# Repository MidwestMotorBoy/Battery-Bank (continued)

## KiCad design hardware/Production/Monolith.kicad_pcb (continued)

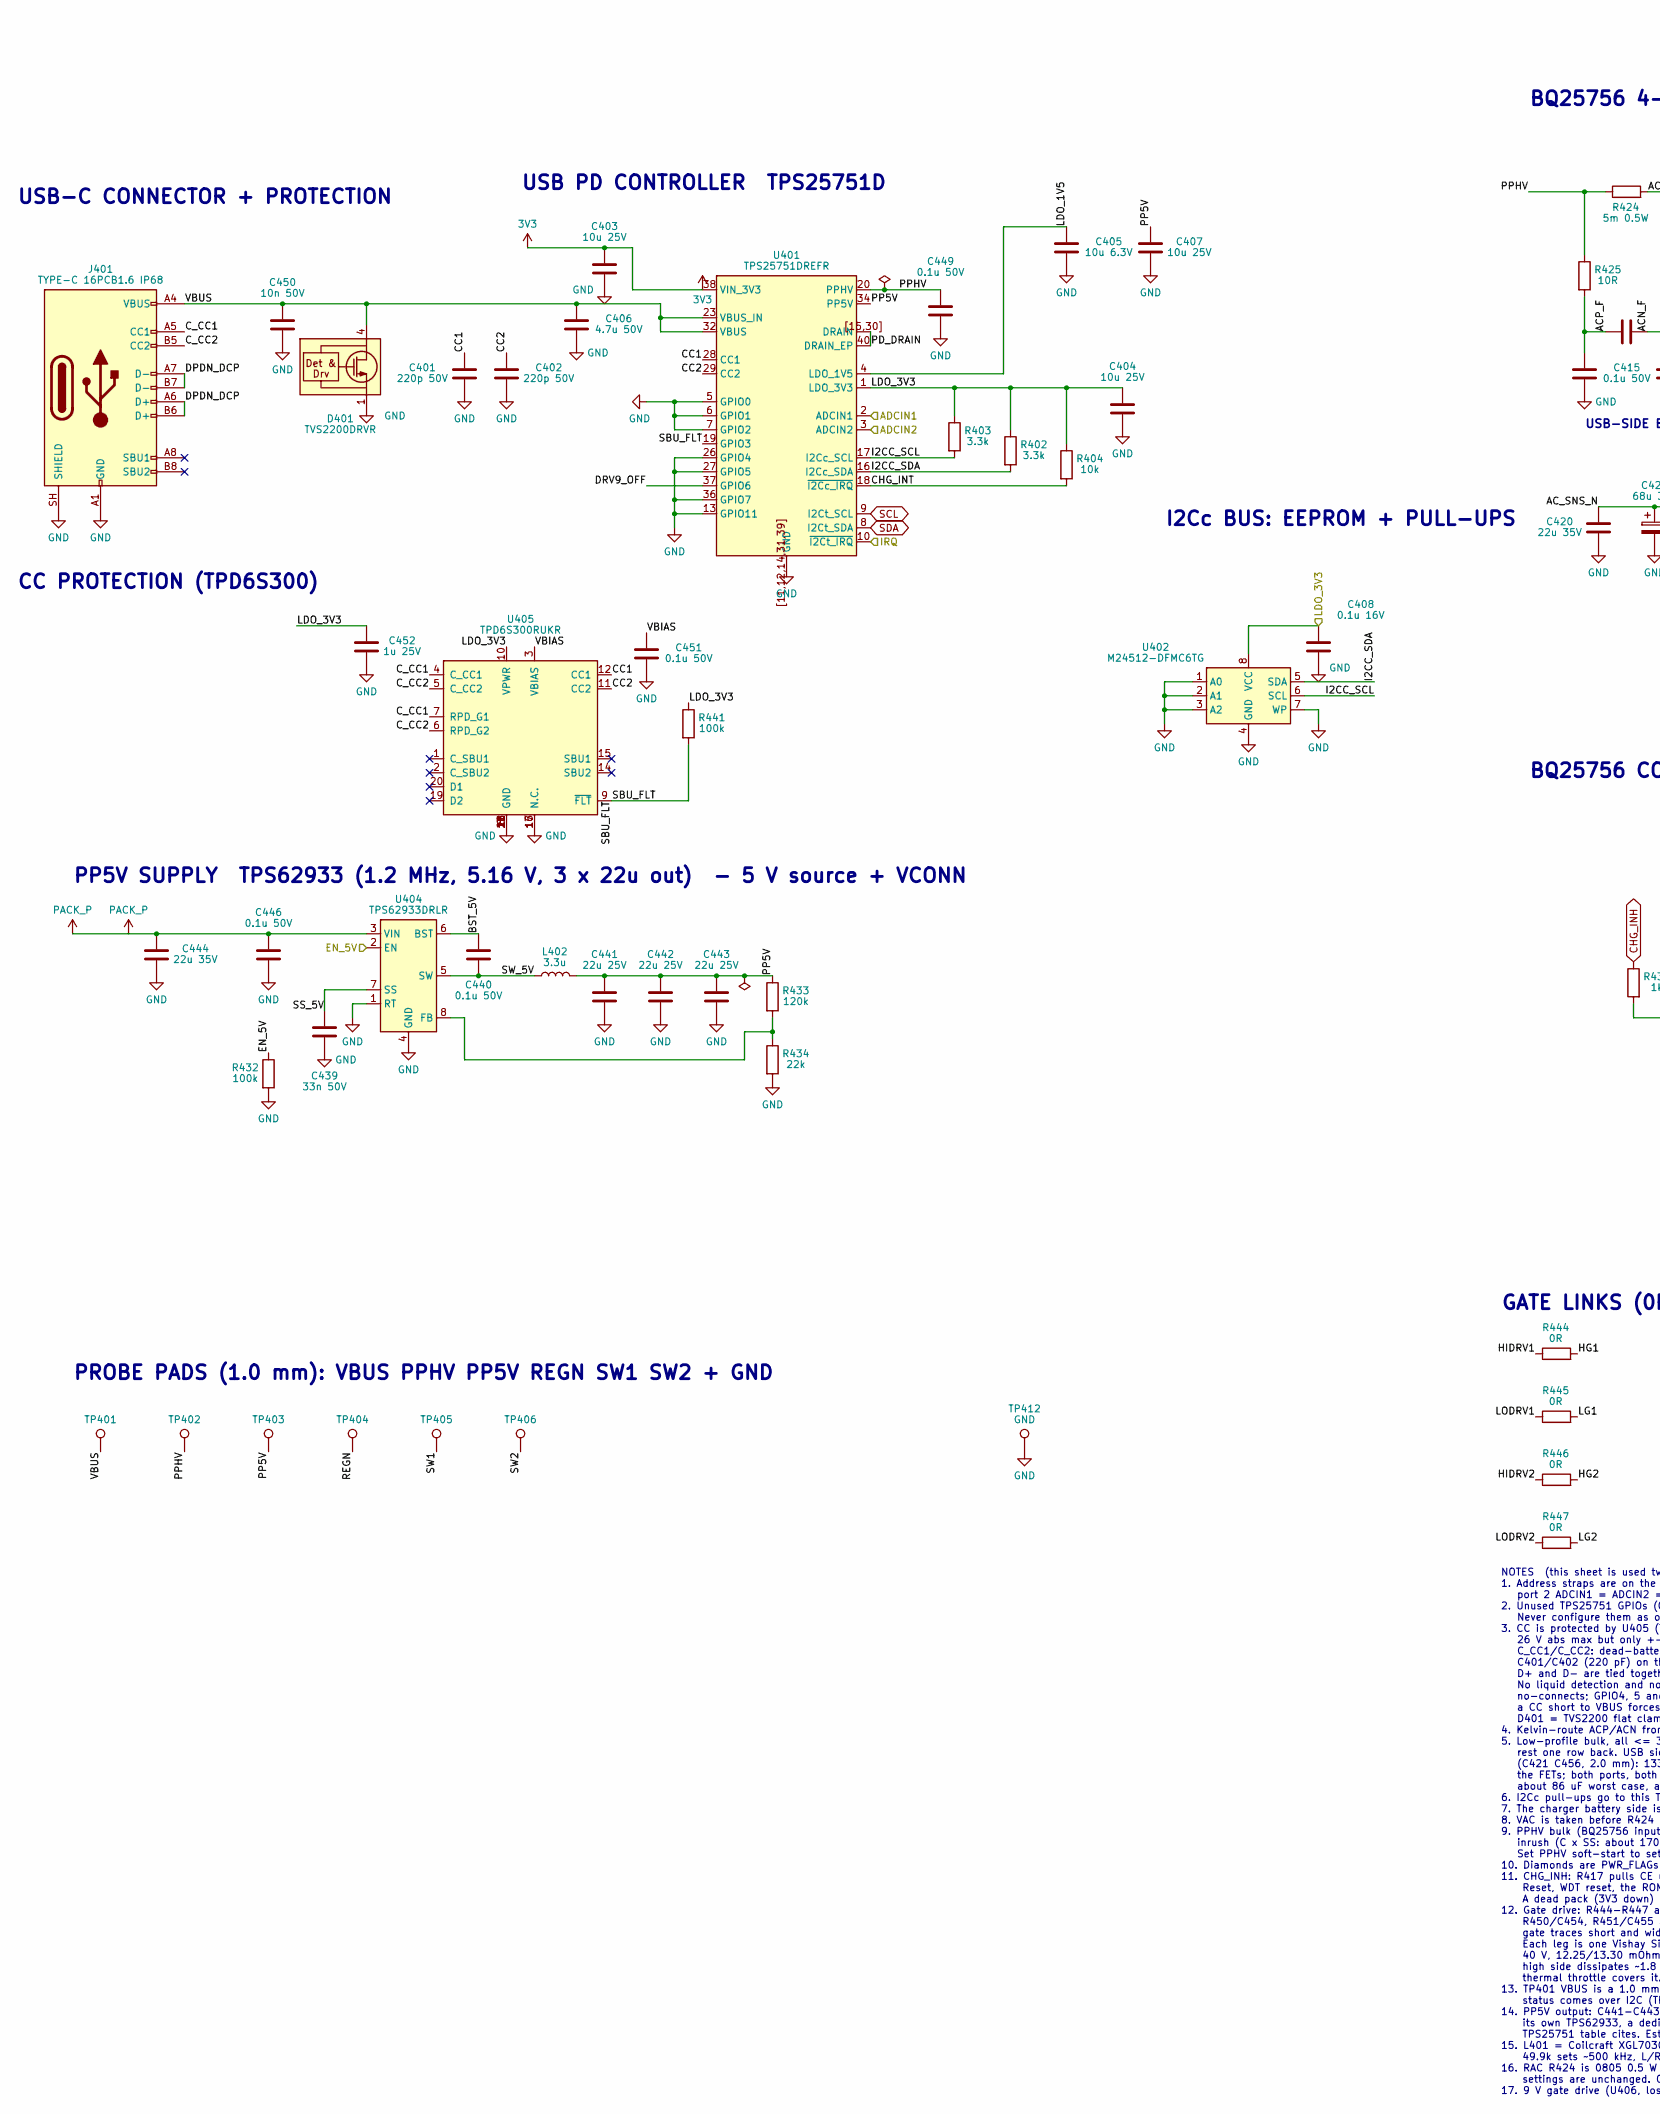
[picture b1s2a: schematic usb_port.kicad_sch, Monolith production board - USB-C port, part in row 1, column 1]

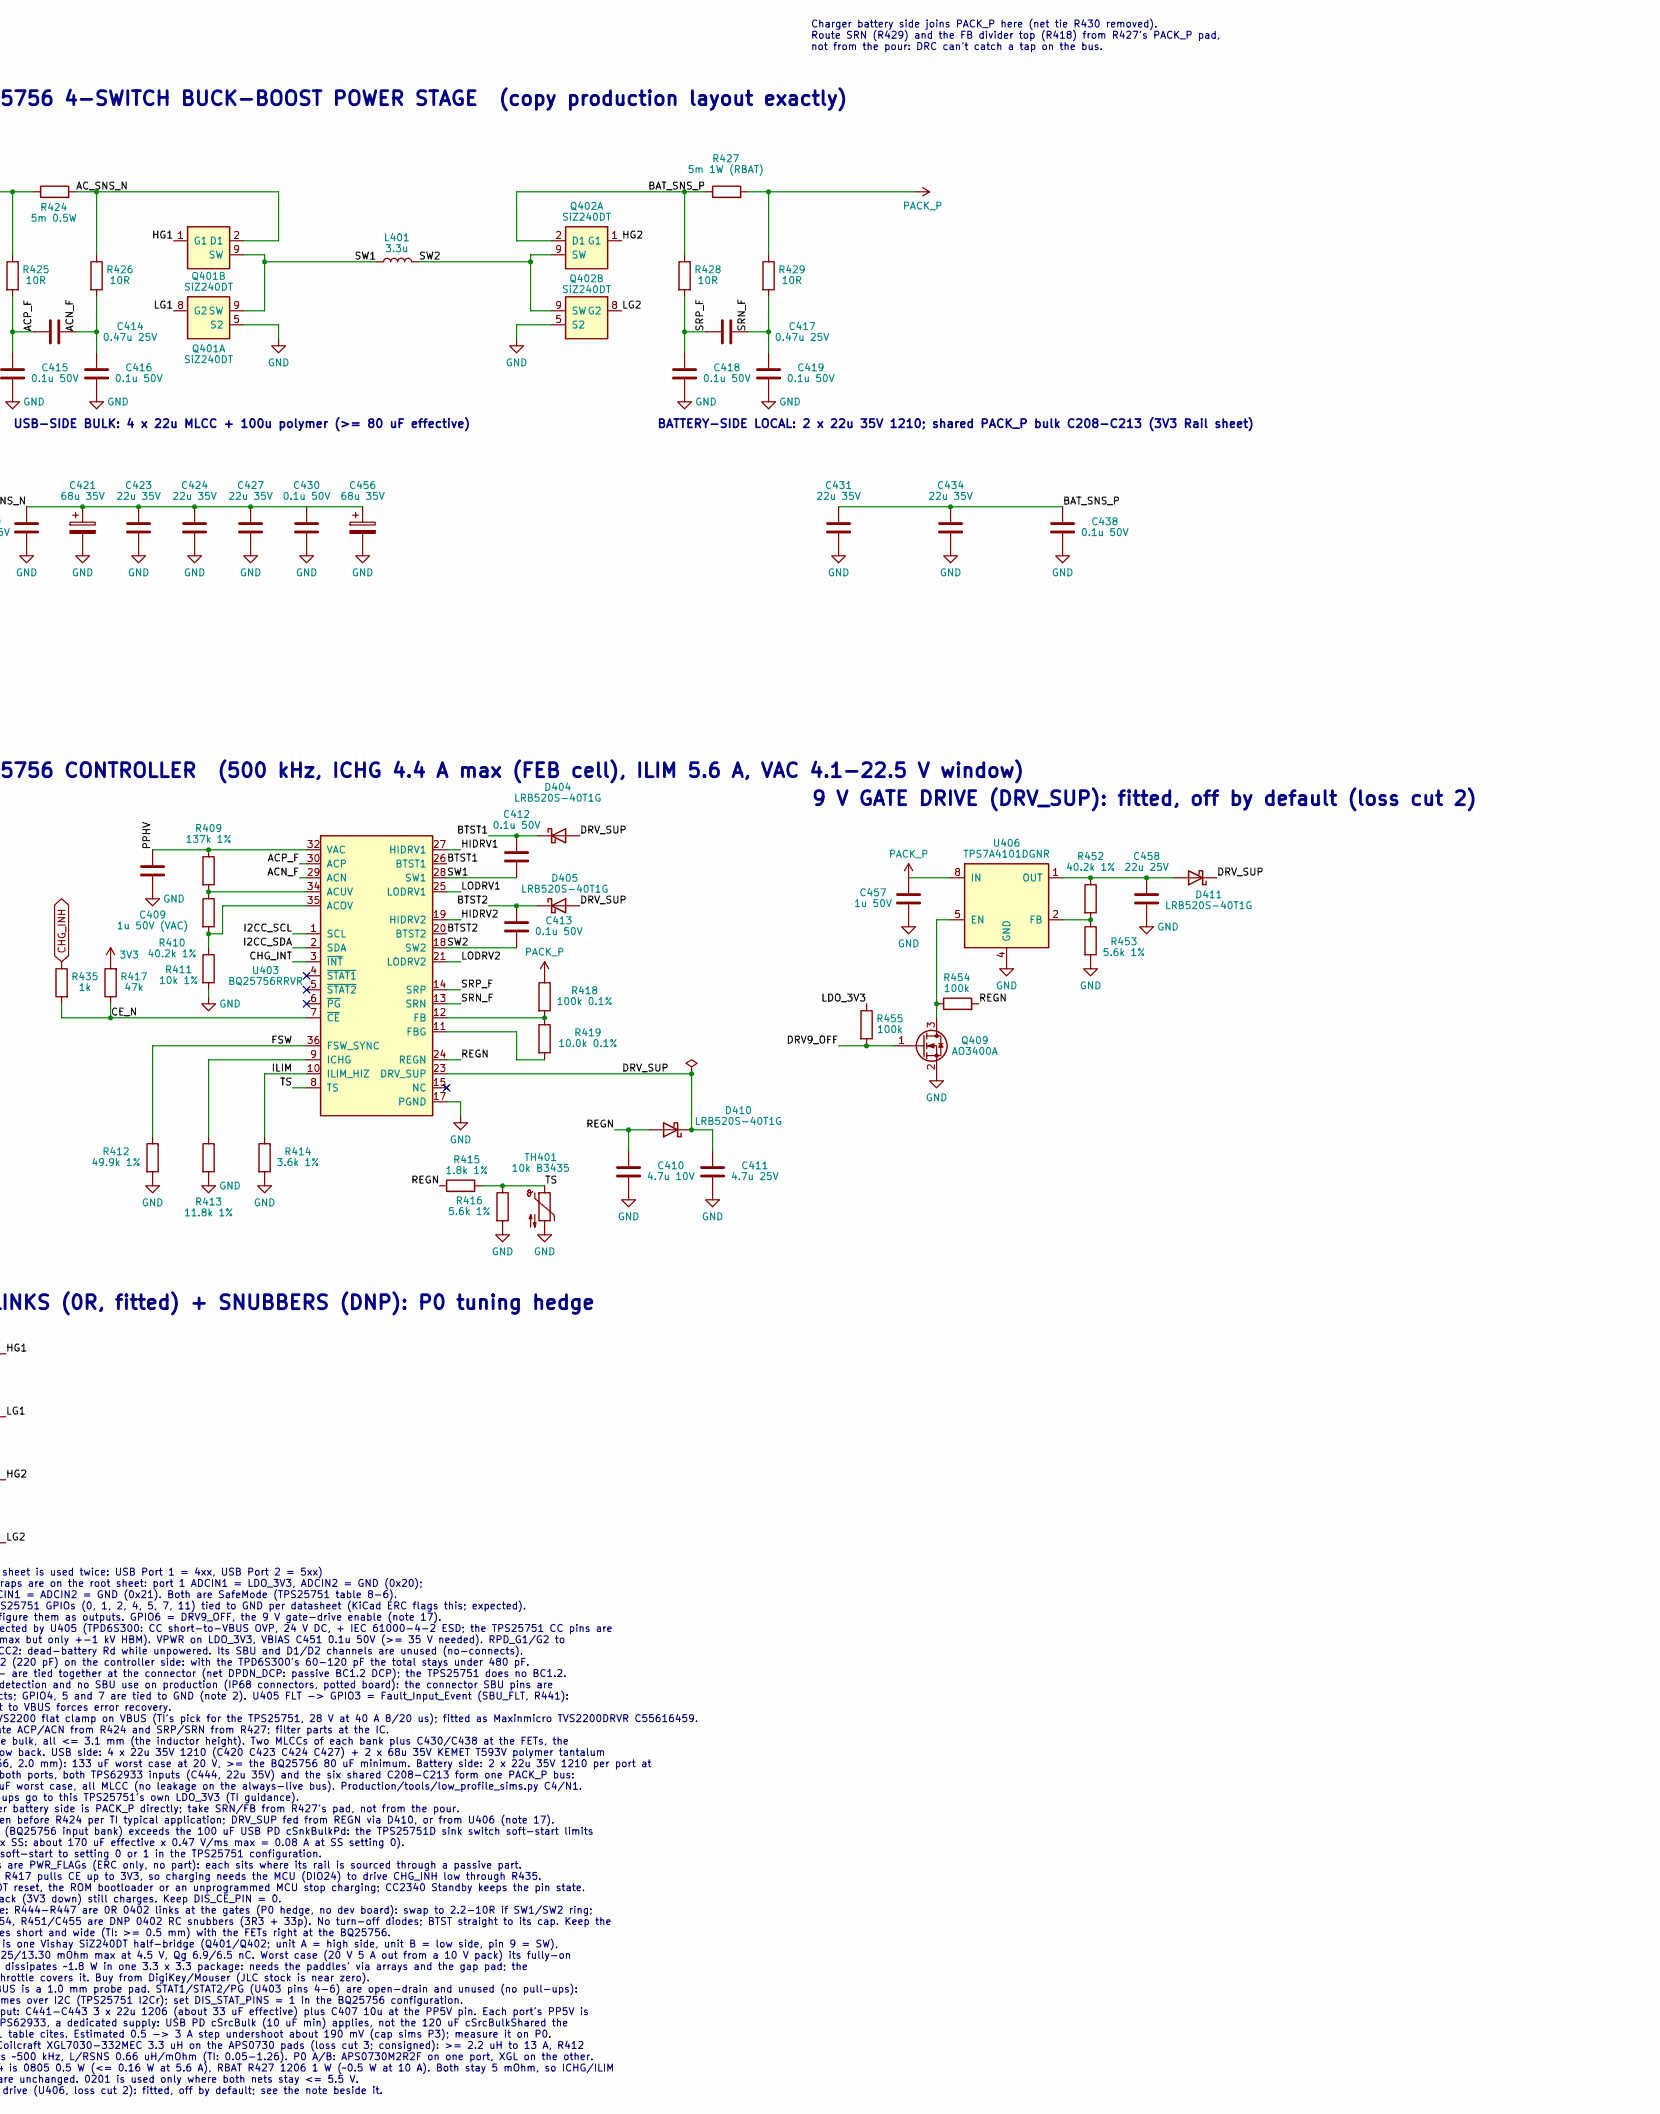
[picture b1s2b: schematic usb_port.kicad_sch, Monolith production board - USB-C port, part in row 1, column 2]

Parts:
C401, C402: 220p 50V; C_0402_1005Metric; MPN 0402B221K500NT; LCSC C1530
C403, C404, C407: 10u 25V; C_0603_1608Metric; MPN CL10A106MA8NRNC; LCSC C96446
C405: 10u 6.3V; C_0402_1005Metric; MPN CL05A106MQ5NUNC; LCSC C15525
C406: 4.7u 50V; C_1206_3216Metric; MPN 1206B475K500NT; LCSC C29823
C408: 0.1u 16V; C_0201_0603Metric; MPN CL03A104KO3NNNC; LCSC C307380
C409: 1u 50V (VAC); C_0603_1608Metric; MPN CL10A105KB8NNNC; LCSC C15849
C410: 4.7u 10V; C_0402_1005Metric; MPN CL05A475MP5NRNC; LCSC C23733
C411: 4.7u 25V; C_0805_2012Metric; MPN CL21A475KAQNNNE; LCSC C1779
C412, C413, C415, C416, C418, C419, C430, C438, C440, C446, C449, C451: 0.1u 50V; C_0402_1005Metric; MPN CL05B104KB54PNC; LCSC C307331
C414, C417: 0.47u 25V; C_0402_1005Metric; MPN CL05A474KA5NNNC; LCSC C92361
C420, C423, C424, C427, C431, C434, C444: 22u 35V; C_1210_3225Metric; MPN GMK325BJ226MM-P; LCSC C778721
C421, C456: 68u 35V; CP_EIA-7343-31_Kemet-D; MPN KEMET T593V686M035APE070 (polymer tanta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
C439: 33n 50V; C_0402_1005Metric; MPN FCC0402B333K500AT; LCSC C7419416
C441, C442, C443: 22u 25V; C_1206_3216Metric; MPN CL31A226KAHNNNE; LCSC C12891
C450: 10n 50V; C_0402_1005Metric; MPN CL05B103KB5NNNC; LCSC C15195
C452: 1u 25V; C_0402_1005Metric; MPN CL05A105KA5NQNC; LCSC C52923
C457: 1u 50V; C_0603_1608Metric; MPN CL10A105KB8NNNC; LCSC C15849
C458: 22u 25V; C_0805_2012Metric; MPN CL21A226MAQNNNE; LCSC C45783
D401: TVS2200DRVR; WSON-6-1EP_2x2mm_P0.65mm_EP1x1.6mm; MPN TVS2200DRVR; LCSC C55616459
D404, D405, D410, D411: LRB520S-40T1G; D_SOD-523; MPN LRB520S-40T1G; LCSC C132124
J401: TYPE-C 16PCB1.6 IP68; USB_C_Receptacle_ShouHan_TYPE-C_16PCB1.6_IP68; MPN TYPE-C 16PCB1.6 IP68 (Shou Han); LCSC C55629729
L401: 3.3u; L_Coilank_APS0730; MPN XGL7030-332MEC (Coilcraft)
L402: 3.3u; L_COILMX_MS0520; MPN EHE05023R3MFB (ABC); LCSC C49248023
Q401, Q402: SiZ240DT; Vishay_PowerPAIR_3x3S; MPN SiZ240DT-T1-GE3 (Vishay); LCSC C3289403
Q409: AO3400A; SOT-23; MPN AO3400A (AOS); LCSC C20917
R402, R403: 3.3k; R_0201_0603Metric; MPN 0201WMF3301TEE; LCSC C270350
R404: 10k; R_0201_0603Metric; MPN 0201WMF1002TEE; LCSC C473048
R409: 137k 1%; R_0402_1005Metric; MPN 0402WGF1373TCE; LCSC C32298
R410, R452: 40.2k 1%; R_0402_1005Metric; MPN 0402WGF4022TCE; LCSC C25893
R411: 10k 1%; R_0402_1005Metric; MPN 0402WGF1002TCE; LCSC C25744
R412: 49.9k 1%; R_0201_0603Metric; MPN 0201WMF4992TEE
R413: 11.8k 1%; R_0402_1005Metric; MPN 0402WGF1182TCE; LCSC C93752
R414: 3.6k 1%; R_0402_1005Metric; MPN 0402WGF3601TCE; LCSC C25891
R415: 1.8k 1%; R_0402_1005Metric; MPN 0402WGF1801TCE; LCSC C25871
R416, R453: 5.6k 1%; R_0402_1005Metric; MPN 0402WGF5601TCE; LCSC C25908
R417: 47k; R_0201_0603Metric; MPN 0201WMF4702TEE; LCSC C270345
R418: 100k 0.1%; R_0402_1005Metric; MPN ERA2AEB104X; LCSC C445619
R419: 10.0k 0.1%; R_0402_1005Metric; MPN ERA2AEB103X; LCSC C191915
R424: 5m 0.5W; R_0805_2012Metric; MPN PA0805FRE470R005L; LCSC C728267
R425, R426, R428, R429: 10R; R_0402_1005Metric; MPN 0402WGF100JTCE; LCSC C25077
R427: 5m 1W (RBAT); R_1206_3216Metric; MPN MA120610FR005MZ (50 ppm); LCSC C252653
R432, R441, R454, R455: 100k; R_0201_0603Metric; MPN 0201WMF1003TEE; LCSC C270364
R433: 120k; R_0402_1005Metric; MPN 0402WGF1203TCE; LCSC C25750
R434: 22k; R_0402_1005Metric; MPN 0402WGF2202TCE; LCSC C25768
R435: 1k; R_0201_0603Metric; MPN 0201WMF1001TEE; LCSC C270365
R444, R445, R446, R447: 0R; R_0402_1005Metric; MPN 0402WGF0000TCE; LCSC C17168
TH401: 10k B3435; R_0402_1005Metric; MPN NCP15XH103F03RC; LCSC C77131
TP401: VBUS; TestPoint_Pad_D1.0mm
TP402: PPHV; TestPoint_Pad_D1.0mm
TP403: PP5V; TestPoint_Pad_D1.0mm
TP404: REGN; TestPoint_Pad_D1.0mm
TP405: SW1; TestPoint_Pad_D1.0mm; MPN RH-S2761-46R (ronghe; Harwin S2761-46R 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
TP406: SW2; TestPoint_Pad_D1.0mm; MPN RH-S2761-46R (ronghe; Harwin S2761-46R 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
TP412: GND; TestPoint_Pad_D1.0mm; MPN RH-S2761-46R (ronghe; Harwin S2761-46R 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
U401: TPS25751DREFR; TI_WQFN-38-2EP_REF0038A_6x4mm_P0.4mm_2oz; MPN TPS25751DREFR; LCSC C30169739
U402: M24512-DFMC6TG; ST_UFDFPN-8-1EP_2x3mm_P0.5mm_EP1.2x1.4mm; MPN M24512-DFMC6TG; LCSC C222237
U403: BQ25756RRVR; TI_VQFN-36-1EP_RRV0036A_5x6mm_P0.5mm; MPN BQ25756RRVR; LCSC C19272232
U404: TPS62933DRLR; SOT-583-8; MPN TPS62933DRLR; LCSC C3200405
U405: TPD6S300RUKR; TI_RUK0020B_WQFN-20-1EP_3x3mm_P0.4mm_EP1.7x1.7mm_Via0.3; MPN TPD6S300RUKR (TI); LCSC C2649810
U406: TPS7A4101DGNR; HVSSOP-8-1EP_3x3mm_P0.65mm_EP1.57x1.89mm; MPN TPS7A4101DGNR (TI); LCSC C111739

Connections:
3V3: C403.1, R417.2, U401.38 (VIN_3V3); also elsewhere on the board
/P1_LDO_3V3: C404.1, C408.1, C452.1, R402.1, R403.1, R404.1, R441.1, R455.1, U401.1 (LDO_3V3), U401.2 (ADCIN1), U402.8 (VCC), U405.10 (VPWR)
/USB Port 1/ACN_F: C414.2, C416.1, R426.2, U403.29 (ACN)
/USB Port 1/ACP_F: C414.1, C415.1, R425.2, U403.30 (ACP)
/USB Port 1/AC_SNS_N: C420.1, C421.1, C423.1, C424.1, C427.1, C430.1, C456.1, Q401.2 (D1), Q401.3 (D1), Q401.4 (D1), R424.2, R426.1
/USB Port 1/BAT_SNS_P: C431.1, C434.1, C438.1, Q402.2 (D1), Q402.3 (D1), Q402.4 (D1), R427.1, R428.1
/USB Port 1/BST_5V: C440.1, U404.6 (BST)
/USB Port 1/BTST1: C412.1, D404.1 (K), U403.26 (BTST1)
/USB Port 1/BTST2: C413.1, D405.1 (K), U403.20 (BTST2)
/USB Port 1/CC1: C401.1, U401.28 (CC1), U405.12 (CC1)
/USB Port 1/CC2: C402.1, U401.29 (CC2), U405.11 (CC2)
/USB Port 1/CE_N: R417.1, R435.2, U403.7 (~CE)
/USB Port 1/CHG_INT: R404.2, U401.18 (~I2Cc_IRQ), U403.3 (~INT)
/USB Port 1/C_CC1: J401.A5 (CC1), U405.4 (C_CC1), U405.7 (RPD_G1)
/USB Port 1/C_CC2: J401.B5 (CC2), U405.5 (C_CC2), U405.6 (RPD_G2)
/USB Port 1/DPDN_DCP: J401.A6 (D+), J401.A7 (D-), J401.B6 (D+), J401.B7 (D-)
/USB Port 1/DRV9_OFF: Q409.1 (G), R455.2, U401.37 (GPIO6)
/USB Port 1/DRV_SUP: C411.1, D404.2 (A), D405.2 (A), D410.1 (K), D411.1 (K), U403.23 (DRV_SUP)
/USB Port 1/FSW: R412.1, U403.36 (FSW_SYNC)
/USB Port 1/HG1: Q401.1 (G1), R444.2
/USB Port 1/HG2: Q402.1 (G1), R446.2
/USB Port 1/HIDRV1: R444.1, U403.27 (HIDRV1)
/USB Port 1/HIDRV2: R446.1, U403.19 (HIDRV2)
/USB Port 1/I2CC_SCL: R403.2, U401.17 (I2Cc_SCL), U402.6 (SCL), U403.1 (SCL)
/USB Port 1/I2CC_SDA: R402.2, U401.16 (I2Cc_SDA), U402.5 (SDA), U403.2 (SDA)
/USB Port 1/ILIM: R414.1, U403.10 (ILIM_HIZ)
/USB Port 1/LDO_1V5: C405.1, U401.4 (LDO_1V5)
/USB Port 1/LG1: Q401.8 (G2), R445.2
/USB Port 1/LG2: Q402.8 (G2), R447.2
/USB Port 1/LODRV1: R445.1, U403.25 (LODRV1)
/USB Port 1/LODRV2: R447.1, U403.21 (LODRV2)
/USB Port 1/PD_DRAIN: U401.15 (DRAIN), U401.30 (DRAIN), U401.40 (DRAIN_EP), U401.[15,30] (DRAIN)
/USB Port 1/PP5V: C407.1, C441.1, C442.1, C443.1, L402.2, R433.1, U401.34 (PP5V)
/USB Port 1/PPHV: C409.1, C449.1, R409.1, R424.1, R425.1, U401.20 (PPHV), U403.32 (VAC), U403.33 (VAC)
/USB Port 1/REGN: C410.1, D410.2 (A), R415.1, R454.2, U403.24 (REGN)
/USB Port 1/SBU_FLT: R441.2, U401.19 (GPIO3), U405.9 (~FLT)
/USB Port 1/SRN_F: C417.2, C419.1, R429.2, U403.13 (SRN)
/USB Port 1/SRP_F: C417.1, C418.1, R428.2, U403.14 (SRP)
/USB Port 1/SS_5V: C439.1, U404.7 (SS)
/USB Port 1/SW1: C412.2, L401.1, Q401.9 (SW), U403.28 (SW1)
/USB Port 1/SW2: C413.2, L401.2, Q402.9 (SW), U403.18 (SW2)
/USB Port 1/SW_5V: C440.2, L402.1, U404.5 (SW)
/USB Port 1/TS: R415.2, R416.1, TH401.1, U403.8 (TS)
/USB Port 1/VBIAS: C451.1, U405.3 (VBIAS)
/USB Port 1/VBUS: C406.1, C450.1, D401.4 (IN), D401.5 (IN), D401.6 (IN), J401.A4 (VBUS), J401.A9 (VBUS), J401.B4 (VBUS), J401.B9 (VBUS), U401.23 (VBUS_IN), U401.32 (VBUS)
CHG_INH: R435.1; also elsewhere on the board
EN_5V1: R432.1, U404.2 (EN); also elsewhere on the board
GND: C401.2, C402.2, C403.2, C404.2, C405.2, C406.2, C407.2, C408.2, C409.2, C410.2, C411.2, C415.2, C416.2, C418.2, C419.2, C420.2, C421.2, C423.2, C424.2, C427.2, C430.2, C431.2, C434.2, C438.2, C439.2, C441.2, C442.2, C443.2, C444.2, C446.2, C449.2, C450.2, C451.2, C452.2, C456.2, C457.2, C458.2, D401.1 (GND), D401.2 (GND), D401.3 (GND), D401.7 (GND), J401.A1 (GND), J401.A12 (GND), J401.B1 (GND), J401.B12 (GND), J401.SH (SHIELD), Q401.5 (S2), Q401.6 (S2), Q401.7 (S2), Q402.5 (S2), Q402.6 (S2), Q402.7 (S2), Q409.2 (S), R411.2, R412.2, R413.2, R414.2, R416.2, R432.2, R434.2, R453.2, TH401.2, TP412.1 (1_1), U401.3 (ADCIN2), U401.5 (GPIO0), U401.6 (GPIO1), U401.7 (GPIO2), U401.11 (GND), U401.12 (GND), U401.13 (GPIO11), U401.14 (GND), U401.26 (GPIO4), U401.27 (GPIO5), U401.31 (GND), U401.36 (GPIO7), U401.39 (GND), U401.[11,12,14,31,39] (GND), U402.1 (A0), U402.2 (A1), U402.3 (A2), U402.4 (GND), U402.7 (WP), U403.17 (PGND), U403.22 (PGND), U403.37 (PGND), U404.1 (RT), U404.4 (GND), U405.8 (GND), U405.13 (GND), U405.16 (N.C.), U405.17 (N.C.), U405.18 (GND), U405.21 (GND), U406.4 (GND), U406.9 (GND); also elsewhere on the board
IRQ_N: U401.10 (~I2Ct_IRQ); also elsewhere on the board
unnamed: C458.1, D411.2 (A), R452.1, U406.1 (OUT)
unnamed: Q409.3 (D), R454.1, U406.5 (EN)
unnamed: R410.2, R411.1, U403.35 (ACOV)
unnamed: R409.2, R410.1, U403.34 (ACUV)
unnamed: R418.2, R419.1, U403.12 (FB)
unnamed: R419.2, U403.11 (FBG)
unnamed: R413.1, U403.9 (ICHG)
unnamed: R433.2, R434.1, U404.8 (FB)
unnamed: R452.2, R453.1, U406.2 (FB)
PACK_P: C444.1, C446.1, C457.1, R418.1, R427.2, R429.1, U404.3 (VIN), U406.8 (IN); also elsewhere on the board
SCL: U401.9 (I2Ct_SCL); also elsewhere on the board
SDA: U401.8 (I2Ct_SDA); also elsewhere on the board

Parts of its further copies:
C501, C502: 220p 50V; C_0402_1005Metric; MPN 0402B221K500NT; LCSC C1530
C503, C504, C507: 10u 25V; C_0603_1608Metric; MPN CL10A106MA8NRNC; LCSC C96446
C505: 10u 6.3V; C_0402_1005Metric; MPN CL05A106MQ5NUNC; LCSC C15525
C506: 4.7u 50V; C_1206_3216Metric; MPN 1206B475K500NT; LCSC C29823
C508: 0.1u 16V; C_0201_0603Metric; MPN CL03A104KO3NNNC; LCSC C307380
C509: 1u 50V (VAC); C_0603_1608Metric; MPN CL10A105KB8NNNC; LCSC C15849
C510: 4.7u 10V; C_0402_1005Metric; MPN CL05A475MP5NRNC; LCSC C23733
C511: 4.7u 25V; C_0805_2012Metric; MPN CL21A475KAQNNNE; LCSC C1779
C512, C513, C515, C516, C518, C519, C530, C538, C540, C546, C549, C551: 0.1u 50V; C_0402_1005Metric; MPN CL05B104KB54PNC; LCSC C307331
C514, C517: 0.47u 25V; C_0402_1005Metric; MPN CL05A474KA5NNNC; LCSC C92361
C520, C523, C524, C527, C531, C534, C544: 22u 35V; C_1210_3225Metric; MPN GMK325BJ226MM-P; LCSC C778721
C521, C556: 68u 35V; CP_EIA-7343-31_Kemet-D; MPN KEMET T593V686M035APE070 (polymer tanta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
C539: 33n 50V; C_0402_1005Metric; MPN FCC0402B333K500AT; LCSC C7419416
C541, C542, C543: 22u 25V; C_1206_3216Metric; MPN CL31A226KAHNNNE; LCSC C12891
C550: 10n 50V; C_0402_1005Metric; MPN CL05B103KB5NNNC; LCSC C15195
C552: 1u 25V; C_0402_1005Metric; MPN CL05A105KA5NQNC; LCSC C52923
C557: 1u 50V; C_0603_1608Metric; MPN CL10A105KB8NNNC; LCSC C15849
C558: 22u 25V; C_0805_2012Metric; MPN CL21A226MAQNNNE; LCSC C45783
D501: TVS2200DRVR; WSON-6-1EP_2x2mm_P0.65mm_EP1x1.6mm; MPN TVS2200DRVR; LCSC C55616459
D504, D505, D510, D511: LRB520S-40T1G; D_SOD-523; MPN LRB520S-40T1G; LCSC C132124
J501: TYPE-C 16PCB1.6 IP68; USB_C_Receptacle_ShouHan_TYPE-C_16PCB1.6_IP68; MPN TYPE-C 16PCB1.6 IP68 (Shou Han); LCSC C55629729
L501: 3.3u; L_Coilank_APS0730; MPN XGL7030-332MEC (Coilcraft)
L502: 3.3u; L_COILMX_MS0520; MPN EHE05023R3MFB (ABC); LCSC C49248023
Q501, Q502: SiZ240DT; Vishay_PowerPAIR_3x3S; MPN SiZ240DT-T1-GE3 (Vishay); LCSC C3289403
Q509: AO3400A; SOT-23; MPN AO3400A (AOS); LCSC C20917
R502, R503: 3.3k; R_0201_0603Metric; MPN 0201WMF3301TEE; LCSC C270350
R504: 10k; R_0201_0603Metric; MPN 0201WMF1002TEE; LCSC C473048
R509: 137k 1%; R_0402_1005Metric; MPN 0402WGF1373TCE; LCSC C32298
R510, R552: 40.2k 1%; R_0402_1005Metric; MPN 0402WGF4022TCE; LCSC C25893
R511: 10k 1%; R_0402_1005Metric; MPN 0402WGF1002TCE; LCSC C25744
R512: 49.9k 1%; R_0201_0603Metric; MPN 0201WMF4992TEE
R513: 11.8k 1%; R_0402_1005Metric; MPN 0402WGF1182TCE; LCSC C93752
R514: 3.6k 1%; R_0402_1005Metric; MPN 0402WGF3601TCE; LCSC C25891
R515: 1.8k 1%; R_0402_1005Metric; MPN 0402WGF1801TCE; LCSC C25871
R516, R553: 5.6k 1%; R_0402_1005Metric; MPN 0402WGF5601TCE; LCSC C25908
R517: 47k; R_0201_0603Metric; MPN 0201WMF4702TEE; LCSC C270345
R518: 100k 0.1%; R_0402_1005Metric; MPN ERA2AEB104X; LCSC C445619
R519: 10.0k 0.1%; R_0402_1005Metric; MPN ERA2AEB103X; LCSC C191915
R524: 5m 0.5W; R_0805_2012Metric; MPN PA0805FRE470R005L; LCSC C728267
R525, R526, R528, R529: 10R; R_0402_1005Metric; MPN 0402WGF100JTCE; LCSC C25077
R527: 5m 1W (RBAT); R_1206_3216Metric; MPN MA120610FR005MZ (50 ppm); LCSC C252653
R532, R541, R554, R555: 100k; R_0201_0603Metric; MPN 0201WMF1003TEE; LCSC C270364
R533: 120k; R_0402_1005Metric; MPN 0402WGF1203TCE; LCSC C25750
R534: 22k; R_0402_1005Metric; MPN 0402WGF2202TCE; LCSC C25768
R535: 1k; R_0201_0603Metric; MPN 0201WMF1001TEE; LCSC C270365
R544, R545, R546, R547: 0R; R_0402_1005Metric; MPN 0402WGF0000TCE; LCSC C17168
TH501: 10k B3435; R_0402_1005Metric; MPN NCP15XH103F03RC; LCSC C77131
TP512: GND; TestPoint_Pad_D1.0mm; MPN RH-S2761-46R (ronghe; Harwin S2761-46R 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
U501: TPS25751DREFR; TI_WQFN-38-2EP_REF0038A_6x4mm_P0.4mm_2oz; MPN TPS25751DREFR; LCSC C30169739
U502: M24512-DFMC6TG; ST_UFDFPN-8-1EP_2x3mm_P0.5mm_EP1.2x1.4mm; MPN M24512-DFMC6TG; LCSC C222237
U503: BQ25756RRVR; TI_VQFN-36-1EP_RRV0036A_5x6mm_P0.5mm; MPN BQ25756RRVR; LCSC C19272232
U504: TPS62933DRLR; SOT-583-8; MPN TPS62933DRLR; LCSC C3200405
U505: TPD6S300RUKR; TI_RUK0020B_WQFN-20-1EP_3x3mm_P0.4mm_EP1.7x1.7mm_Via0.3; MPN TPD6S300RUKR (TI); LCSC C2649810
U506: TPS7A4101DGNR; HVSSOP-8-1EP_3x3mm_P0.65mm_EP1.57x1.89mm; MPN TPS7A4101DGNR (TI); LCSC C111739

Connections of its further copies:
3V3: C503.1, R517.2, U501.38 (VIN_3V3); also elsewhere on the board
/USB Port 2/ACN_F: C514.2, C516.1, R526.2, U503.29 (ACN)
/USB Port 2/ACP_F: C514.1, C515.1, R525.2, U503.30 (ACP)
/USB Port 2/AC_SNS_N: C520.1, C521.1, C523.1, C524.1, C527.1, C530.1, C556.1, Q501.2 (D1), Q501.3 (D1), Q501.4 (D1), R524.2, R526.1
/USB Port 2/BAT_SNS_P: C531.1, C534.1, C538.1, Q502.2 (D1), Q502.3 (D1), Q502.4 (D1), R527.1, R528.1
/USB Port 2/BST_5V: C540.1, U504.6 (BST)
/USB Port 2/BTST1: C512.1, D504.1 (K), U503.26 (BTST1)
/USB Port 2/BTST2: C513.1, D505.1 (K), U503.20 (BTST2)
/USB Port 2/CC1: C501.1, U501.28 (CC1), U505.12 (CC1)
/USB Port 2/CC2: C502.1, U501.29 (CC2), U505.11 (CC2)
/USB Port 2/CE_N: R517.1, R535.2, U503.7 (~CE)
/USB Port 2/CHG_INT: R504.2, U501.18 (~I2Cc_IRQ), U503.3 (~INT)
/USB Port 2/C_CC1: J501.A5 (CC1), U505.4 (C_CC1), U505.7 (RPD_G1)
/USB Port 2/C_CC2: J501.B5 (CC2), U505.5 (C_CC2), U505.6 (RPD_G2)
/USB Port 2/DPDN_DCP: J501.A6 (D+), J501.A7 (D-), J501.B6 (D+), J501.B7 (D-)
/USB Port 2/DRV9_OFF: Q509.1 (G), R555.2, U501.37 (GPIO6)
/USB Port 2/DRV_SUP: C511.1, D504.2 (A), D505.2 (A), D510.1 (K), D511.1 (K), U503.23 (DRV_SUP)
/USB Port 2/FSW: R512.1, U503.36 (FSW_SYNC)
/USB Port 2/HG1: Q501.1 (G1), R544.2
/USB Port 2/HG2: Q502.1 (G1), R546.2
/USB Port 2/HIDRV1: R544.1, U503.27 (HIDRV1)
/USB Port 2/HIDRV2: R546.1, U503.19 (HIDRV2)
/USB Port 2/I2CC_SCL: R503.2, U501.17 (I2Cc_SCL), U502.6 (SCL), U503.1 (SCL)
/USB Port 2/I2CC_SDA: R502.2, U501.16 (I2Cc_SDA), U502.5 (SDA), U503.2 (SDA)
/USB Port 2/ILIM: R514.1, U503.10 (ILIM_HIZ)
/USB Port 2/LDO_1V5: C505.1, U501.4 (LDO_1V5)
/USB Port 2/LDO_3V3: C504.1, C508.1, C552.1, R502.1, R503.1, R504.1, R541.1, R555.1, U501.1 (LDO_3V3), U502.8 (VCC), U505.10 (VPWR)
/USB Port 2/LG1: Q501.8 (G2), R545.2
/USB Port 2/LG2: Q502.8 (G2), R547.2
/USB Port 2/LODRV1: R545.1, U503.25 (LODRV1)
/USB Port 2/LODRV2: R547.1, U503.21 (LODRV2)
/USB Port 2/PD_DRAIN: U501.15 (DRAIN), U501.30 (DRAIN), U501.40 (DRAIN_EP)
/USB Port 2/PP5V: C507.1, C541.1, C542.1, C543.1, L502.2, R533.1, U501.34 (PP5V)
/USB Port 2/PPHV: C509.1, C549.1, R509.1, R524.1, R525.1, U501.20 (PPHV), U503.32 (VAC), U503.33 (VAC)
/USB Port 2/REGN: C510.1, D510.2 (A), R515.1, R554.2, U503.24 (REGN)
/USB Port 2/SBU_FLT: R541.2, U501.19 (GPIO3), U505.9 (~FLT)
/USB Port 2/SRN_F: C517.2, C519.1, R529.2, U503.13 (SRN)
/USB Port 2/SRP_F: C517.1, C518.1, R528.2, U503.14 (SRP)
/USB Port 2/SS_5V: C539.1, U504.7 (SS)
/USB Port 2/SW1: C512.2, L501.1, Q501.9 (SW), U503.28 (SW1)
/USB Port 2/SW2: C513.2, L501.2, Q502.9 (SW), U503.18 (SW2)
/USB Port 2/SW_5V: C540.2, L502.1, U504.5 (SW)
/USB Port 2/TS: R515.2, R516.1, TH501.1, U503.8 (TS)
/USB Port 2/VBIAS: C551.1, U505.3 (VBIAS)
/USB Port 2/VBUS: C506.1, C550.1, D501.4 (IN), D501.5 (IN), D501.6 (IN), J501.A4 (VBUS), J501.A9 (VBUS), J501.B4 (VBUS), J501.B9 (VBUS), U501.23 (VBUS_IN), U501.32 (VBUS)
CHG_INH: R535.1; also elsewhere on the board
EN_5V2: R532.1, U504.2 (EN); also elsewhere on the board
GND: C501.2, C502.2, C503.2, C504.2, C505.2, C506.2, C507.2, C508.2, C509.2, C510.2, C511.2, C515.2, C516.2, C518.2, C519.2, C520.2, C521.2, C523.2, C524.2, C527.2, C530.2, C531.2, C534.2, C538.2, C539.2, C541.2, C542.2, C543.2, C544.2, C546.2, C549.2, C550.2, C551.2, C552.2, C556.2, C557.2, C558.2, D501.1 (GND), D501.2 (GND), D501.3 (GND), D501.7 (GND), J501.A1 (GND), J501.A12 (GND), J501.B1 (GND), J501.B12 (GND), J501.SH (SHIELD), Q501.5 (S2), Q501.6 (S2), Q501.7 (S2), Q502.5 (S2), Q502.6 (S2), Q502.7 (S2), Q509.2 (S), R511.2, R512.2, R513.2, R514.2, R516.2, R532.2, R534.2, R553.2, TH501.2, TP512.1 (1_1), U501.2 (ADCIN1), U501.3 (ADCIN2), U501.5 (GPIO0), U501.6 (GPIO1), U501.7 (GPIO2), U501.11 (GND), U501.12 (GND), U501.13 (GPIO11), U501.14 (GND), U501.26 (GPIO4), U501.27 (GPIO5), U501.31 (GND), U501.36 (GPIO7), U501.39 (GND), U502.1 (A0), U502.2 (A1), U502.3 (A2), U502.4 (GND), U502.7 (WP), U503.17 (PGND), U503.22 (PGND), U503.37 (PGND), U504.1 (RT), U504.4 (GND), U505.8 (GND), U505.13 (GND), U505.16 (N.C.), U505.17 (N.C.), U505.18 (GND), U505.21 (GND), U506.4 (GND), U506.9 (GND); also elsewhere on the board
IRQ_N: U501.10 (~I2Ct_IRQ); also elsewhere on the board
unnamed: C558.1, D511.2 (A), R552.1, U506.1 (OUT)
unnamed: Q509.3 (D), R554.1, U506.5 (EN)
unnamed: R510.2, R511.1, U503.35 (ACOV)
unnamed: R509.2, R510.1, U503.34 (ACUV)
unnamed: R518.2, R519.1, U503.12 (FB)
unnamed: R519.2, U503.11 (FBG)
unnamed: R513.1, U503.9 (ICHG)
unnamed: R533.2, R534.1, U504.8 (FB)
unnamed: R552.2, R553.1, U506.2 (FB)
PACK_P: C544.1, C546.1, C557.1, R518.1, R527.2, R529.1, U504.3 (VIN), U506.8 (IN); also elsewhere on the board
SCL: U501.9 (I2Ct_SCL); also elsewhere on the board
SDA: U501.8 (I2Ct_SDA); also elsewhere on the board

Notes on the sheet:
PP5V SUPPLY TPS62933 (1.2 MHz, 5.16 V, 3 x 22u out) - 5 V source + VCONN
GATE LINKS (0R, fitted) + SNUBBERS (DNP): P0 tuning hedge
BATTERY-SIDE LOCAL: 2 x 22u 35V 1210; shared PACK_P bulk C208-C213 (3V3 Rail sheet)
9 V GATE DRIVE (DRV_SUP): fitted, off by default (loss cut 2)
BQ25756 CONTROLLER (500 kHz, ICHG 4.4 A max (FEB cell), ILIM 5.6 A, VAC 4.1-22.5 V window)
I2Cc BUS: EEPROM + PULL-UPS
PROBE PADS (1.0 mm): VBUS PPHV PP5V REGN SW1 SW2 + GND
USB-SIDE BULK: 4 x 22u MLCC + 100u polymer (>= 80 uF effective)
Charger battery side joins PACK_P here (net tie R430 removed). Route SRN (R429) and the FB divider top (R418) from R427's PACK_P pad, not from the pour: DRC can't catch a tap on the bus.
USB PD CONTROLLER TPS25751D
USB-C CONNECTOR + PROTECTION
BQ25756 4-SWITCH BUCK-BOOST POWER STAGE (copy production layout exactly)
NOTES (this sheet is used twice: USB Port 1 = 4xx, USB Port 2 = 5xx) 1. Address straps are on the root sheet: port 1 ADCIN1 = LDO_3V3, ADCIN2 = GND (0x20); port 2 ADCIN1 = ADCIN2 = GND (0x21). Both are SafeMode (TPS25751 table 8-6). 2. Unused TPS25751 GPIOs (0, 1, 2, 4, 5, 7, 11) tied to GND per da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
CC PROTECTION (TPD6S300)
